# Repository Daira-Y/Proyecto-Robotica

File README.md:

# Proyecto-Robotica
Smart Trash Can

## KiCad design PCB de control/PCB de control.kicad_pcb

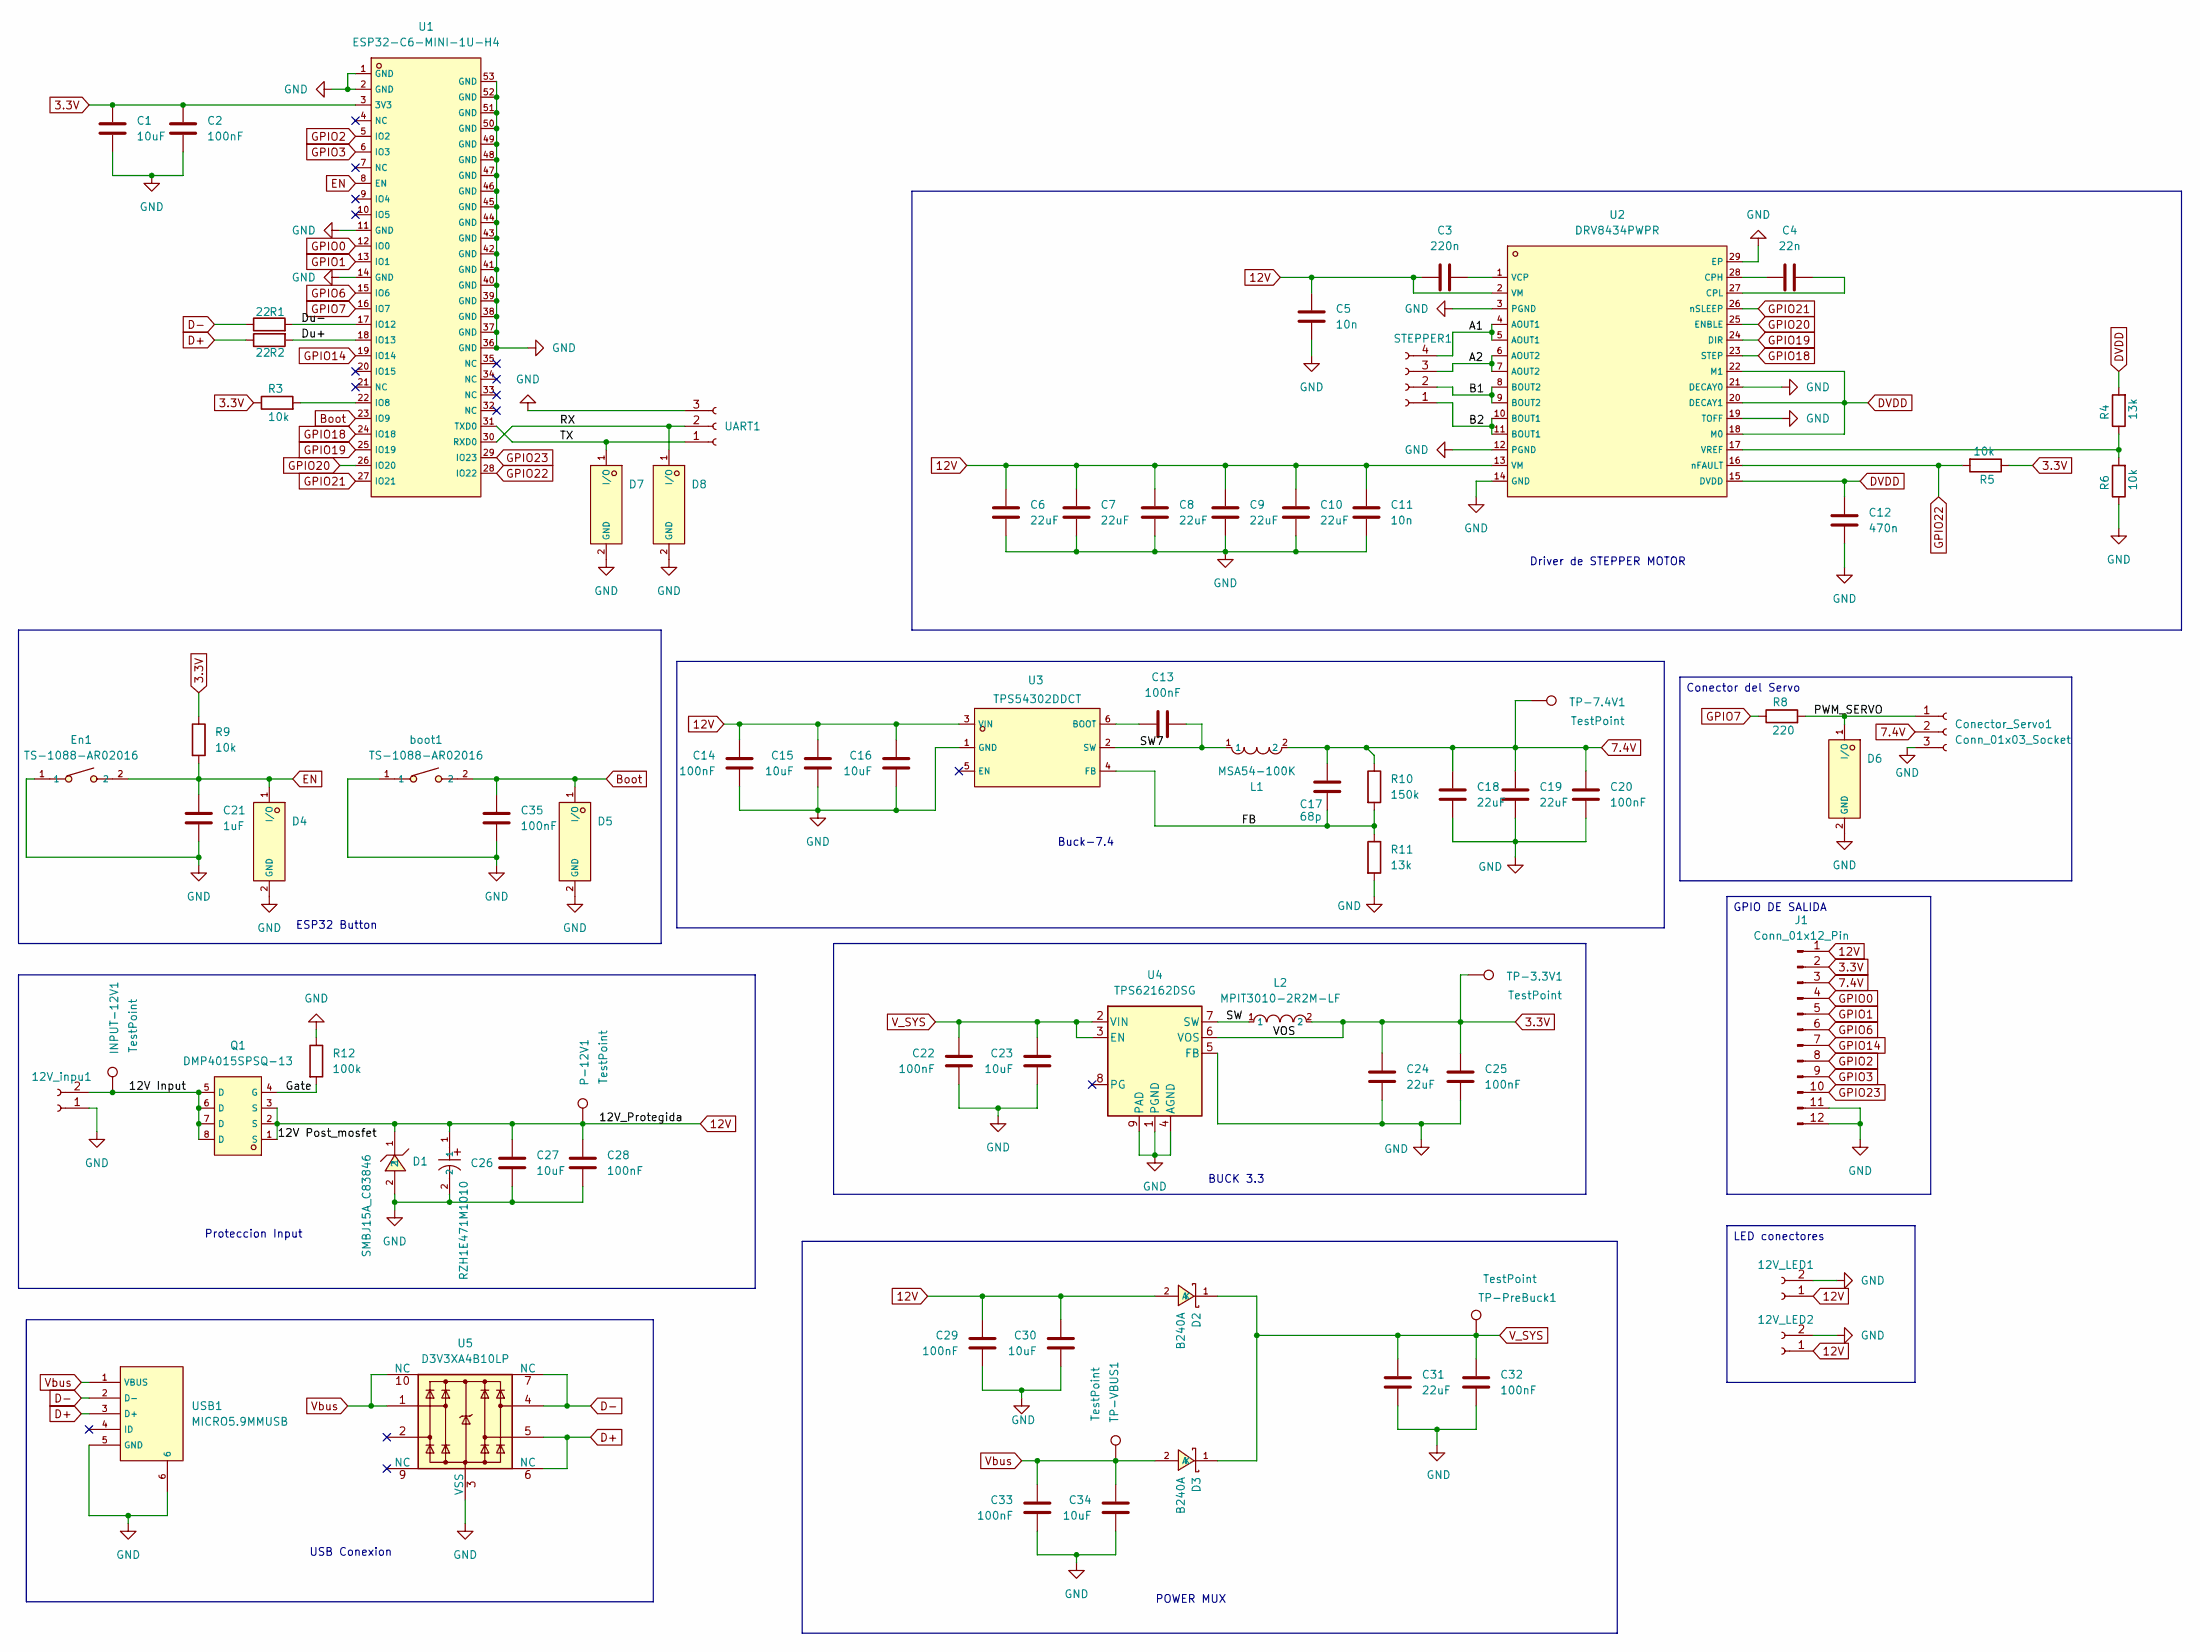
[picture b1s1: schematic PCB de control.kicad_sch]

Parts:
12V_LED1, 12V_LED2: Conn_01x02_Socket; Molex_KK-254_AE-6410-02A_1x02_P2.54mm_Vertical
12V_inpu1: Conn_01x02_Socket; TerminalBlock_Phoenix_MKDS-1,5-2-5.08_1x02_P5.08mm_Horizont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
C1: 10uF; C_0603_1608Metric
C2, C35: 100nF; C_0603_1608Metric
C3: 220n; C_0805_2012Metric
C4: 22n; C_0805_2012Metric
C5: 10n; C_0805_2012Metric
C6, C7, C8, C9, C10, C18, C19, C24, C31: 22uF; C_0805_2012Metric
C11: 10n; C_0603_1608Metric
C12: 470n; C_0805_2012Metric
C13, C14, C20, C22, C25, C28, C29, C32, C33: 100nF; C_0805_2012Metric
C15, C16, C23, C27, C30, C34: 10uF; C_0805_2012Metric
C17: 68p; C_0805_2012Metric
C21: 1uF; C_0603_1608Metric
C26: RZH1E471M1010; C47117667_CAP-SMD_BD10_0-L10_3-W10_3-LS11_0-FD; LCSC C47117667
Conector_Servo1: Conn_01x03_Socket; Molex_KK-254_AE-6410-03A_1x03_P2.54mm_Vertical
D1: SMBJ15A_C83846; C83846_SMB_L4_6-W3_6-LS5_3-RD; LCSC C83846
D2, D3: B240A; C39358_SMA_L4_3-W2_6-LS5_2-RD; LCSC C39358
D4, D5, D6, D7, D8: ESD321DPYR_C2868952; C2868952_X1SON-2_L1_0-W0_6-P0_65-RD-1; LCSC C2868952
En1: TS-1088-AR02016; C720477_SW-SMD_L3_9-W3_0-P4_45; LCSC C720477
INPUT-12V1: TestPoint; Pin_D0.7mm_L6.5mm_W1.8mm_FlatFork
J1: Conn_01x12_Pin; PinHeader_1x12_P2.54mm_Vertical
L1: MSA54-100K; C2840579_IND-SMD_L5_8-W5_2; LCSC C2840579
L2: MPIT3010-2R2M-LF; C281241_IND-SMD_L3_0-W3_0_ABG03A; LCSC C281241
P-12V1: TestPoint; Pin_D0.7mm_L6.5mm_W1.8mm_FlatFork
Q1: DMP4015SPSQ-13; C384564_POWERDI5060-8_L5_8-W4_9-P1_27-LS6_2-BL; LCSC C384564
R1, R2: 22; R_0603_1608Metric_Pad0.98x0.95mm_HandSolder
R3, R5, R6, R9: 10k; R_0603_1608Metric_Pad0.98x0.95mm_HandSolder
R4: 13k; R_0603_1608Metric_Pad0.98x0.95mm_HandSolder
R8: 220; R_0603_1608Metric_Pad0.98x0.95mm_HandSolder
R10: 150k; R_0805_2012Metric_Pad1.20x1.40mm_HandSolder
R11: 13k; R_0805_2012Metric_Pad1.20x1.40mm_HandSolder
R12: 100k; R_0805_2012Metric_Pad1.20x1.40mm_HandSolder
STEPPER1: Conn_01x04_Socket; Molex_KK-254_AE-6410-04A_1x04_P2.54mm_Vertical
TP-3.3V1, TP-7.4V1: TestPoint; Pin_D0.7mm_L6.5mm_W1.8mm_FlatFork
TP-PreBuck1: TestPoint; Pin_D0.7mm_L6.5mm_W1.8mm_FlatFork
TP-VBUS1: TestPoint; Pin_D0.7mm_L6.5mm_W1.8mm_FlatFork
U1: ESP32-C6-MINI-1U-H4; C20627095_WIFIM-SMD_61P-L13_2-W12_5-P0_80; LCSC C20627095
U2: DRV8434PWPR; C3681245_HTSSOP-28_L9_7-W4_4-P0_65-LS6_4-BL-EP-5; LCSC C3681245
U3: TPS54302DDCT; C129370_TSOT-23-6_L2_9-W1_6-P0_95-LS2_8-BR; LCSC C129370
U4: TPS62162DSG; WSON-8-1EP_2x2mm_P0.5mm_EP0.9x1.6mm_ThermalVias
U5: D3V3XA4B10LP; Diodes_UDFN-10_1.0x2.5mm_P0.5mm
UART1: Conn_01x03_Socket; Molex_KK-254_AE-6410-03A_1x03_P2.54mm_Vertical
USB1: MICRO5.9MMUSB; C393940_MICRO-USB-SMD_5P-P0_65-H-F_MICRO5_9MMUSB; LCSC C393940
boot1: TS-1088-AR02016; C720477_SW-SMD_L3_9-W3_0-P4_45; LCSC C720477

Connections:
3.3V: C1.1, C2.1, C24.1, C25.1, J1.2, L2.2, R3.1, R5.1, R9.1, TP-3.3V1.1, U1.3 (3V3), U4.6 (VOS)
7.4V: C17.1, C18.1, C19.1, C20.1, Conector_Servo1.2, J1.3, L1.2, R10.1, TP-7.4V1.1
12V: 12V_LED1.1, 12V_LED2.1, C3.1, C5.2, C6.1, C7.1, C8.1, C9.1, C10.1, C11.2, C14.1, C15.1, C16.1, C26.1, C27.1, C28.1, C29.1, C30.1, D1.1, D2.2 (A), J1.1, P-12V1.1, Q1.1 (S), Q1.2 (S), Q1.3 (S), U2.2 (VM), U2.13 (VM), U3.3 (VIN)
/12V Input: 12V_inpu1.2, INPUT-12V1.1, Q1.5 (D), Q1.6 (D), Q1.7 (D), Q1.8 (D)
/A1: STEPPER1.4, U2.4 (AOUT1), U2.5 (AOUT1)
/A2: STEPPER1.3, U2.6 (AOUT2), U2.7 (AOUT2)
/B1: STEPPER1.2, U2.8 (BOUT2), U2.9 (BOUT2)
/B2: STEPPER1.1, U2.10 (BOUT1), U2.11 (BOUT1)
/Du+: R2.2, U1.18 (IO13)
/Du-: R1.2, U1.17 (IO12)
/FB: C17.2, R10.2, R11.1, U3.4 (FB)
/Gate: Q1.4 (G), R12.2
/PWM_SERVO: Conector_Servo1.1, D6.1 (I/O), R8.2
/RX: D8.1 (I/O), U1.30 (RXD0), UART1.2
/SW: L2.1, U4.7 (SW)
/SW7: C13.1, L1.1, U3.2 (SW)
/TX: D7.1 (I/O), U1.31 (TXD0), UART1.1
Boot: C35.1, D5.1 (I/O), U1.23 (IO9), boot1.2
D+: R2.1, U5.5, U5.6 (NC), USB1.3 (D+)
D-: R1.1, U5.4, U5.7 (NC), USB1.2 (D-)
DVDD: C12.2, R4.2, U2.15 (DVDD), U2.18 (M0), U2.20 (DECAY1), U2.22 (M1)
EN: C21.1, D4.1 (I/O), En1.2, R9.2, U1.8 (EN)
GND: 12V_LED1.2, 12V_LED2.2, 12V_inpu1.1, C1.2, C2.2, C5.1, C6.2, C7.2, C8.2, C9.2, C10.2, C11.1, C12.1, C14.2, C15.2, C16.2, C18.2, C19.2, C20.2, C21.2, C22.2, C23.2, C24.2, C25.2, C26.2, C27.2, C28.2, C29.2, C30.2, C31.2, C32.2, C33.2, C34.2, C35.2, Conector_Servo1.3, D1.2, D4.2 (GND), D5.2 (GND), D6.2 (GND), D7.2 (GND), D8.2 (GND), En1.1, J1.11, J1.12, R6.1, R11.2, R12.1, U1.1 (GND), U1.2 (GND), U1.11 (GND), U1.14 (GND), U1.36 (GND), U1.37 (GND), U1.38 (GND), U1.39 (GND), U1.40 (GND), U1.41 (GND), U1.42 (GND), U1.43 (GND), U1.44 (GND), U1.45 (GND), U1.46 (GND), U1.47 (GND), U1.48 (GND), U1.49 (GND), U1.50 (GND), U1.51 (GND), U1.52 (GND), U1.53 (GND), U2.3 (PGND), U2.12 (PGND), U2.14 (GND), U2.19 (TOFF), U2.21 (DECAY0), U2.29 (EP), U3.1 (GND), U4.1 (PGND), U4.4 (AGND), U4.5 (FB), U4.9 (PAD), U5.3 (VSS), U5.8 (VSS), UART1.3, USB1.5 (GND), USB1.6, boot1.1
GPIO0: J1.4, U1.12 (IO0)
GPIO1: J1.5, U1.13 (IO1)
GPIO2: J1.8, U1.5 (IO2)
GPIO3: J1.9, U1.6 (IO3)
GPIO6: J1.6, U1.15 (IO6)
GPIO7: R8.1, U1.16 (IO7)
GPIO14: J1.7, U1.19 (IO14)
GPIO18: U1.24 (IO18), U2.23 (STEP)
GPIO19: U1.25 (IO19), U2.24 (DIR)
GPIO20: U1.26 (IO20), U2.25 (ENBLE)
GPIO21: U1.27 (IO21), U2.26 (nSLEEP)
GPIO22: R5.2, U1.28 (IO22), U2.16 (nFAULT)
GPIO23: J1.10, U1.29 (IO23)
unnamed: R3.2, U1.22 (IO8)
unnamed: C4.1, U2.28 (CPH)
unnamed: C4.2, U2.27 (CPL)
unnamed: C3.2, U2.1 (VCP)
unnamed: R4.1, R6.2, U2.17 (VREF)
unnamed: C13.2, U3.6 (BOOT)
V_SYS: C22.1, C23.1, C31.1, C32.1, D2.1 (K), D3.1 (K), TP-PreBuck1.1, U4.2 (VIN), U4.3 (EN)
Vbus: C33.1, C34.1, D3.2 (A), TP-VBUS1.1, U5.1, U5.10 (NC), USB1.1 (VBUS)

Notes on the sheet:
BUCK 3.3
Buck-7.4
Proteccion Input
ESP32 Button
POWER MUX
USB Conexion
Driver de STEPPER MOTOR
GPIO DE SALIDA
Conector del Servo
LED conectores

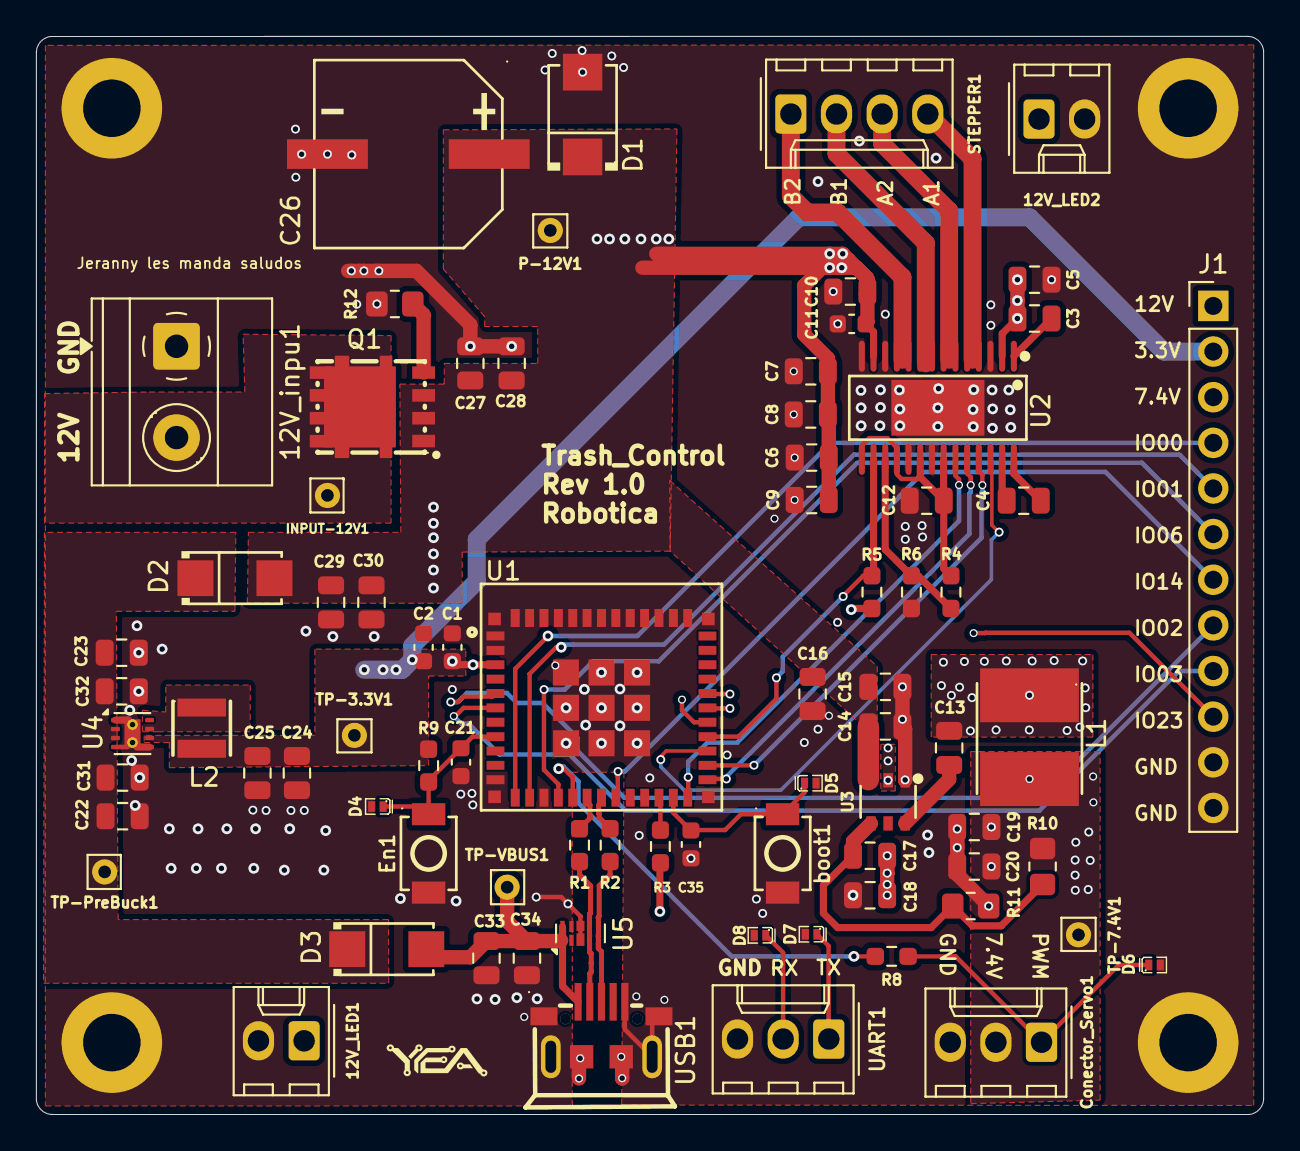
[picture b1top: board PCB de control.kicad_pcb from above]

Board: 4 copper layers, 68.3 x 60.0 mm, 78 parts (0 on the bottom side), 44 nets.

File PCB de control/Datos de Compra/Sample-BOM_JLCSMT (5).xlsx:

Comment | Designator | Footprint | JLCPCB Part #（optional）
DMP4015SPSQ-13 | Q1 | C384564_POWERDI5060-8_L5_8-W4_9-P1_27-LS6_2-BL
10k | R5,R3,R6,R9 | R_0603_1608Metric_Pad0.98x0.95mm_HandSolder
22uF | C31,C9,C6,C10,C8,C24,C7,C19,C18 | C_0805_2012Metric
100nF | C33,C20,C22,C29,C13,C14,C28,C32,C25 | C_0805_2012Metric
TestPoint | TP-PreBuck1,INPUT-12V1,TP-3.3V1,P-12V1,TP-7.4V1,TP-VBUS1 | Pin_D0.7mm_L6.5mm_W1.8mm_FlatFork
TS-1088-AR02016 | boot1,En1 | C720477_SW-SMD_L3_9-W3_0-P4_45
Conn_01x03_Socket | Conector_Servo1,UART1 | Molex_KK-254_AE-6410-03A_1x03_P2.54mm_Vertical
Conn_01x02_Socket | 12V_LED2,12V_LED1 | Molex_KK-254_AE-6410-02A_1x02_P2.54mm_Vertical
Conn_01x02_Socket | 12V_inpu1 | TerminalBlock_Phoenix_MKDS-1,5-2-5.08_1x02_P5.08mm_Horizontal
10uF | C16,C34,C15,C23,C30,C27 | C_0805_2012Metric
TPS54302DDCT | U3 | C129370_TSOT-23-6_L2_9-W1_6-P0_95-LS2_8-BR
DRV8434PWPR | U2 | C3681245_HTSSOP-28_L9_7-W4_4-P0_65-LS6_4-BL-EP-5
13k | R4 | R_0603_1608Metric_Pad0.98x0.95mm_HandSolder
22 | R2,R1 | R_0603_1608Metric_Pad0.98x0.95mm_HandSolder
ESD321DPYR_C2868952 | D7,D4,D5,D8,D6 | C2868952_X1SON-2_L1_0-W0_6-P0_65-RD-1
B240A | D3,D2 | C39358_SMA_L4_3-W2_6-LS5_2-RD
SMBJ15A_C83846 | D1 | C83846_SMB_L4_6-W3_6-LS5_3-RD
10uF | C1 | C_0603_1608Metric
MSA54-100K | L1 | C2840579_IND-SMD_L5_8-W5_2
TPS62162DSG | U4 | WSON-8-1EP_2x2mm_P0.5mm_EP0.9x1.6mm_ThermalVias
100nF | C2,C35 | C_0603_1608Metric
10n | C11 | C_0603_1608Metric
MPIT3010-2R2M-LF | L2 | C281241_IND-SMD_L3_0-W3_0_ABG03A
MICRO5.9MMUSB | USB1 | C393940_MICRO-USB-SMD_5P-P0_65-H-F_MICRO5_9MMUSB
1uF | C21 | C_0603_1608Metric
220 | R8 | R_0603_1608Metric_Pad0.98x0.95mm_HandSolder
68p | C17 | C_0805_2012Metric
220n | C3 | C_0805_2012Metric
22n | C4 | C_0805_2012Metric
ESP32-C6-MINI-1U-H4 | U1 | C20627095_WIFIM-SMD_61P-L13_2-W12_5-P0_80
150k | R10 | R_0805_2012Metric_Pad1.20x1.40mm_HandSolder
Conn_01x12_Pin | J1 | PinHeader_1x12_P2.54mm_Vertical
RZH1E471M1010 | C26 | C47117667_CAP-SMD_BD10_0-L10_3-W10_3-LS11_0-FD
100k | R12 | R_0805_2012Metric_Pad1.20x1.40mm_HandSolder
Conn_01x04_Socket | STEPPER1 | Molex_KK-254_AE-6410-04A_1x04_P2.54mm_Vertical
10n | C5 | C_0805_2012Metric
13k | R11 | R_0805_2012Metric_Pad1.20x1.40mm_HandSolder
470n | C12 | C_0805_2012Metric
D3V3XA4B10LP | U5 | Diodes_UDFN-10_1.0x2.5mm_P0.5mm
